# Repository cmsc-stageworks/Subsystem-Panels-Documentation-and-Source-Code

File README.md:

# SubsystemPanelsDocumentationAndSourceCode
Source Code and documentation for all the Subsystem Panels, some of the videos and the libraries folder for arduino wouldnt upload, so I suggest checking with Mr. Porter for those

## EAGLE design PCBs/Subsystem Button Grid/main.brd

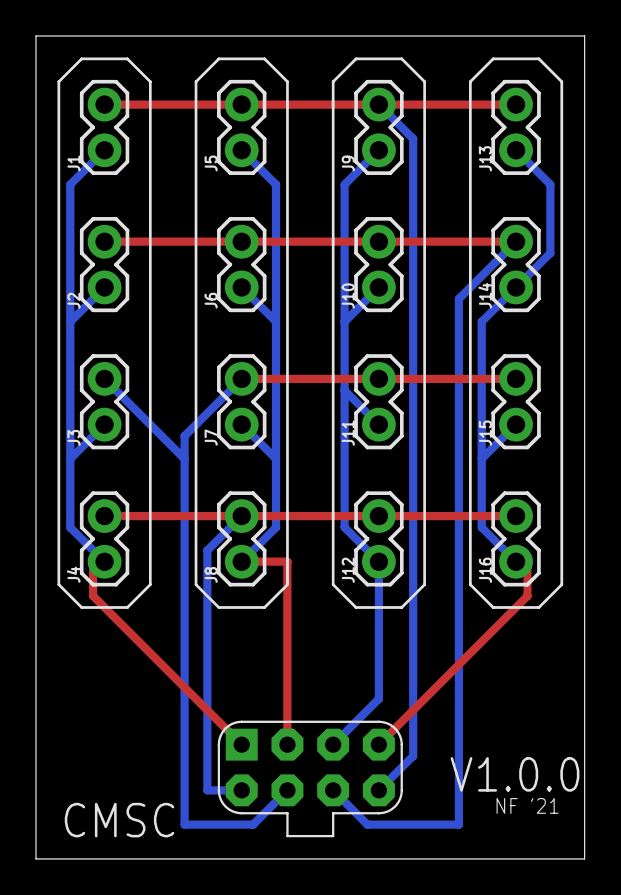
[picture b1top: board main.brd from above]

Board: 2 copper layers, 30.5 x 45.7 mm, 17 parts (0 on the bottom side), 8 nets.

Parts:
J1, J2, J3, J4, J5, J6, J7, J8, J9, J10, J11, J12, J13, J14, J15, J16: 1X02
U$1: BUTTON_GRID_HEADER; BUTTON_GRID_HEADER_RIBBON_CONNECTOR

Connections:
unnamed: J1.1, J2.1, J3.1, J4.1, U$1.P1
unnamed: J5.1, J6.1, J7.1, J8.1, U$1.P2
unnamed: J9.1, J10.1, J11.1, J12.1, U$1.P3
unnamed: J13.1, J14.1, J15.1, J16.1, U$1.P4
PA: J4.2, J8.2, J12.2, J16.2, U$1.PA
PB: J3.2, J7.2, J11.2, J15.2, U$1.PB
PC: J2.2, J6.2, J10.2, J14.2, U$1.PC
PD: J1.2, J5.2, J9.2, J13.2, U$1.PD

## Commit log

2022-03-24 Added Documentation
    Enjoy!
2024-09-19 Moved PCB Directory to the repo
    I've been working on these and I just needed to add them
2024-09-19 Cleaned up main pcb folder
2024-09-19 Removed useless files
2024-09-19 Created a new folder for the new 4th iteration of the PCB
    I need to adjust the SPI Header to allow for the reset signal to be sent, along with this I will just route an extra pin from the mega to the touch SPI Interface, just in case someone wants to take a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
2024-09-19 Started Work on SPI Board Rework
    need to change the size of the board for the 2.8" screen and also change the connector out, as well as use the raw parts for the bi-directional logic level converter.
2024-09-20 Updates to V3 of the SPI Breakout Board
2024-09-20 Finished SPI Breakout Board V3
2024-09-20 Added Resistor Values
2024-09-20 Fixed some labels on the silkscreen
2024-09-20 Minor visual glitch fix on silkscreen
2024-09-20 Fixed drill hole positions
2024-10-03 Fixed the headers to include reset for the SPI interface and expansion for future touch control if wanted
2024-10-09 various fabrication outputs
2024-10-16 added neopixel stabalization
    added capacitor slot and resistor slot, both are optional but can be added to increase stability.
2024-10-17 Added Parts List and files for button board
2024-10-17 opened a file and github detects a change of some kind
2024-10-21 added a piece I forgot to the parts list
2025-01-18 more work
2025-02-02 updated some files, added panel code
2025-03-02 started work on updated ethernet controller
2025-03-02 Moved Compiling enviornments to VS Code
2025-03-16 updated subsystem code
2025-05-10 Updated Subsystem code
    - now has webpage for setting MQTT address
    - communication via MQTT to central server
    - panel name is now stored on SD card
2025-05-20 Updated PCBs
    - Updated PCBs for the subsystem main
    - Started work on an idea for a new panel (on my own time)
2025-08-07 Work on new main pcb
2025-08-13 adjusted schematic and started PCB Work
2025-08-16 Continued PCB Layout
2025-09-20 moved main board to new repo
2025-09-20 Moved New Panel to its own repo
